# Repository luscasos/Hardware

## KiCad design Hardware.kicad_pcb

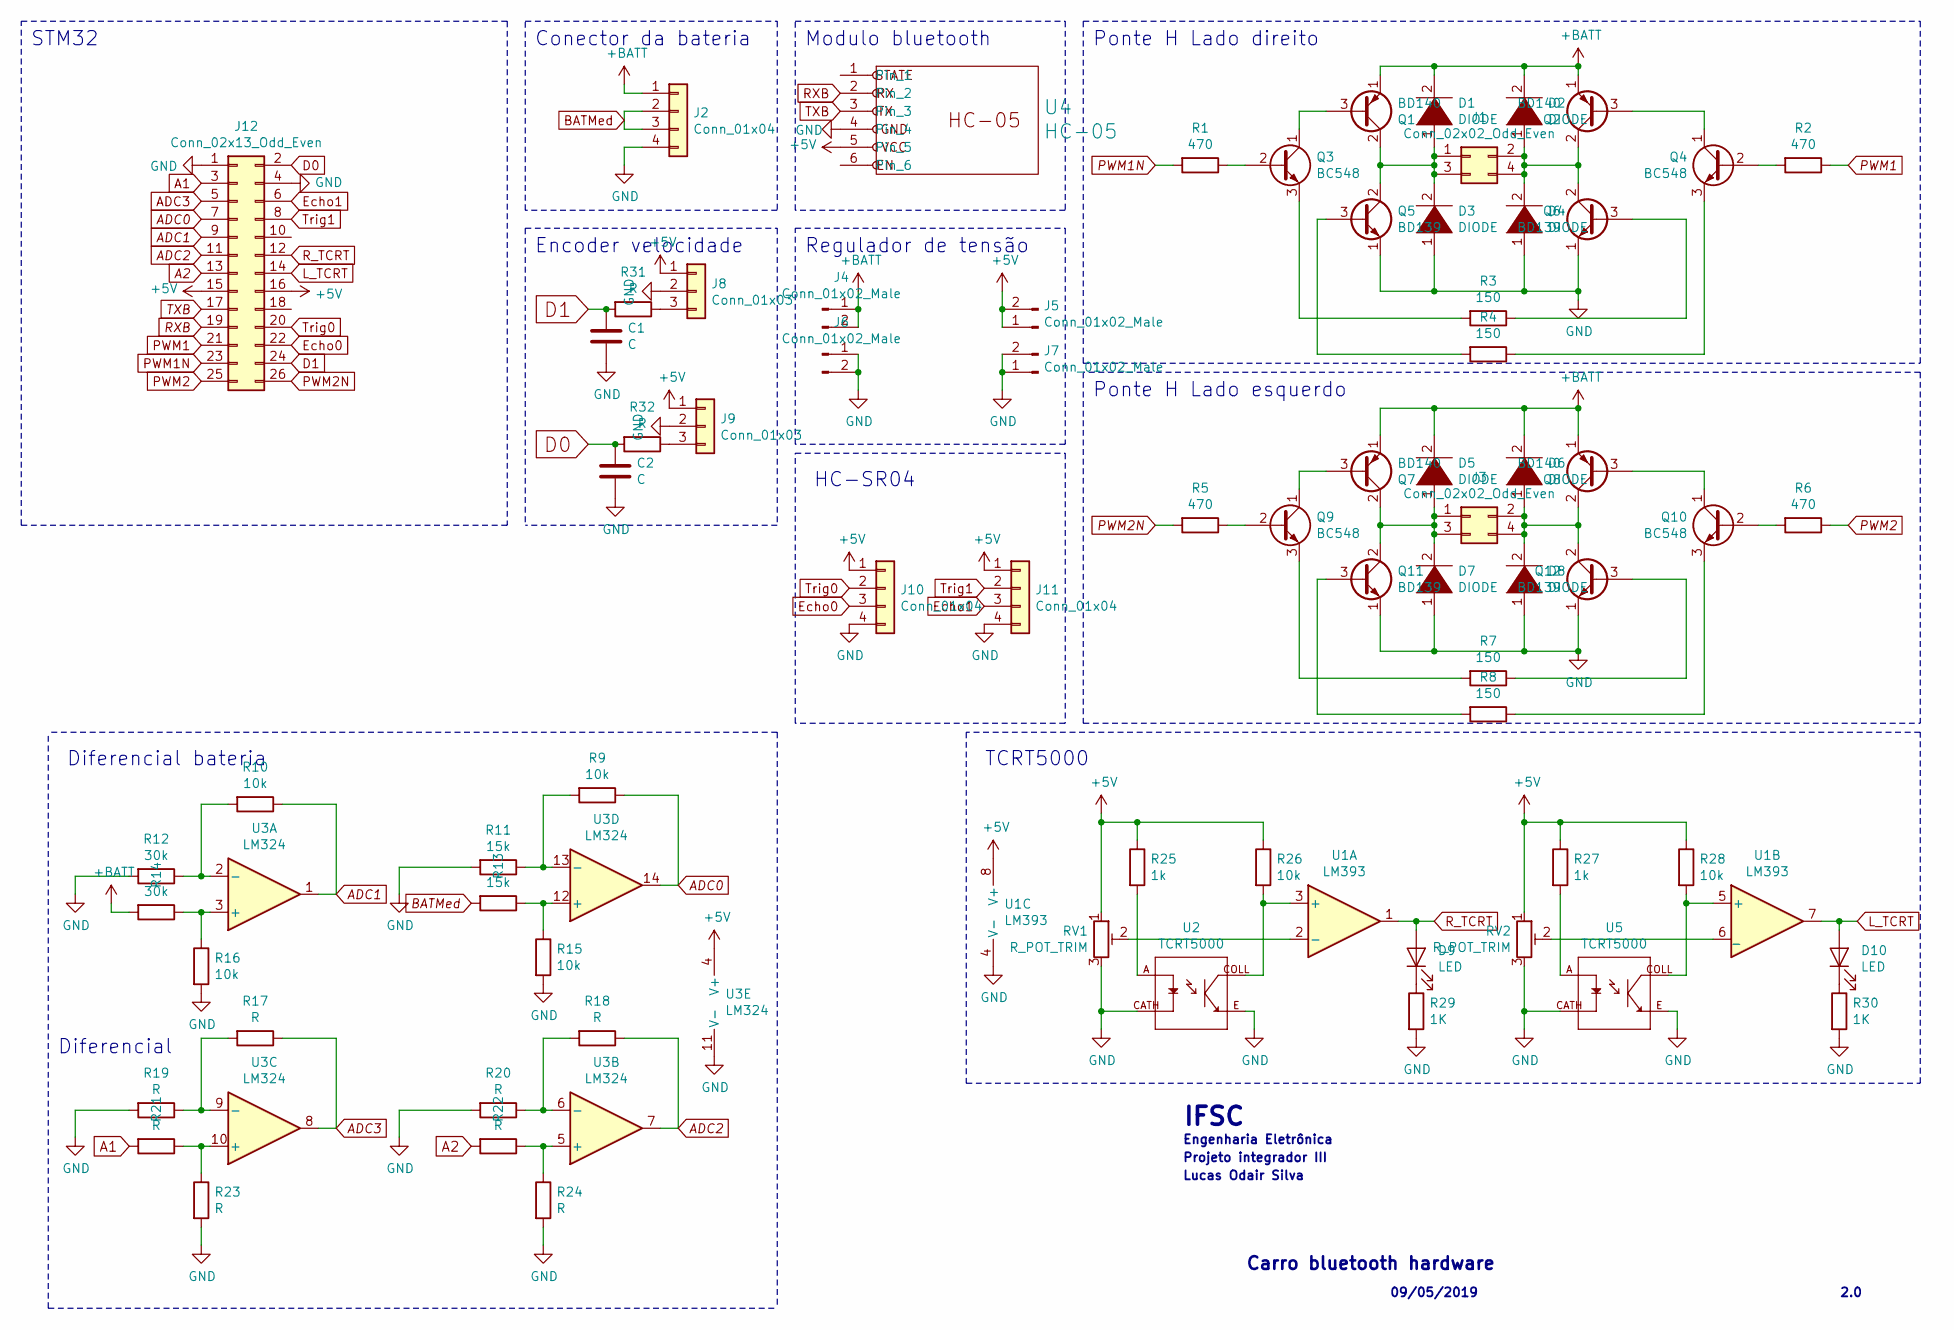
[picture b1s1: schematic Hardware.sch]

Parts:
C1, C2: C; C_0805_2012Metric_Pad1.15x1.40mm_HandSolder
D1, D2, D3, D4, D5, D6, D7, D8: DIODE; D_A-405_P2.54mm_Vertical_AnodeUp
D9, D10: LED; LED_0805_2012Metric
J1, J3: Conn_02x02_Odd_Even; PinHeader_2x02_P2.54mm_Vertical
J2, J10, J11: Conn_01x04; PinHeader_1x04_P2.54mm_Vertical
J4, J5, J6, J7: Conn_01x02_Male; PinSocket_1x02_P2.54mm_Vertical
J8, J9: Conn_01x03; PinHeader_1x03_P2.54mm_Vertical
J12: Conn_02x13_Odd_Even; PinSocket_2x13_P2.54mm_Vertical
Q1, Q2, Q7, Q8: BD140; TO-126-3_Vertical
Q3, Q4, Q9, Q10: BC548; TO-92_Inline_Wide
Q5, Q6, Q11, Q12: BD139; TO-126-3_Vertical
R1, R2, R5, R6: 470; R_0805_2012Metric
R3, R4, R7, R8: 150; R_0805_2012Metric
R9, R10, R15, R16, R26, R28: 10k; R_0805_2012Metric
R11, R13: 15k; R_0805_2012Metric
R12, R14: 30k; R_0805_2012Metric
R17, R18, R19, R20, R21, R22, R23, R24: R; R_0805_2012Metric
R25, R27: 1k; R_0805_2012Metric
R29, R30: 1K; R_0805_2012Metric
R31, R32: R; R_0805_2012Metric_Pad1.15x1.40mm_HandSolder
RV1, RV2: R_POT_TRIM; Potentiometer_Piher_PT-10-H01_Horizontal
U1: LM393
U2, U5: TCRT5000; OPTO_TCRT5000
U3: LM324; SOIC-14_3.9x8.7mm_P1.27mm
U4: HC-05; PinHeader_1x06_P2.54mm_Horizontal

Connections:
+5V: J5.1, J5.2, J8.1, J9.1, J10.1, J11.1, J12.15, J12.16, R25.1, R26.1, R27.1, R28.1, RV1.1, RV2.1, U1.8 (V+), U3.4 (V+), U4.5
+BATT: D1.2 (A), D2.2 (A), D5.2 (A), D6.2 (A), J2.1, J4.1, J4.2, Q1.1 (E), Q2.1 (E), Q7.1 (E), Q8.1 (E), R14.2
A1: J12.3, R21.2
A2: J12.13, R22.2
ADC0: J12.7, R9.1, U3.14
ADC1: J12.9, R10.1, U3.1
ADC2: J12.11, R18.1, U3.7
ADC3: J12.5, R17.1, U3.8
BATMed: J2.2, J2.3, R13.2
D0: C2.1, J12.2, R32.2
D1: C1.1, J12.24, R31.2
Echo0: J10.3, J12.22
Echo1: J11.3, J12.6
GND: C1.2, C2.2, D3.1 (K), D4.1 (K), D7.1 (K), D8.1 (K), J2.4, J6.1, J6.2, J7.1, J7.2, J8.2, J9.2, J10.4, J11.4, J12.1, J12.4, Q5.1 (E), Q6.1 (E), Q11.1 (E), Q12.1 (E), R11.2, R12.2, R15.2, R16.2, R19.2, R20.2, R23.2, R24.2, R29.2, R30.2, RV1.3, RV2.3, U1.4 (V-), U2.CATH, U2.E, U3.11 (V-), U4.4, U5.CATH, U5.E
L_TCRT: D10.2 (A), J12.14, U1.7
unnamed: D1.1 (K), D3.2 (A), J1.1, J1.3, Q1.2 (C), Q5.2 (C)
unnamed: D2.1 (K), D4.2 (A), J1.2, J1.4, Q2.2 (C), Q6.2 (C)
unnamed: D5.1 (K), D7.2 (A), J3.1, J3.3, Q7.2 (C), Q11.2 (C)
unnamed: D6.1 (K), D8.2 (A), J3.2, J3.4, Q8.2 (C), Q12.2 (C)
unnamed: D9.1 (K), R29.1
unnamed: D10.1 (K), R30.1
unnamed: J8.3, R31.1
unnamed: J9.3, R32.1
unnamed: Q1.3 (B), Q3.1 (C)
unnamed: Q2.3 (B), Q4.1 (C)
unnamed: Q3.2 (B), R1.1
unnamed: Q3.3 (E), R3.2
unnamed: Q4.2 (B), R2.2
unnamed: Q4.3 (E), R4.1
unnamed: Q5.3 (B), R4.2
unnamed: Q6.3 (B), R3.1
unnamed: Q7.3 (B), Q9.1 (C)
unnamed: Q9.2 (B), R5.1
unnamed: Q9.3 (E), R7.2
unnamed: Q8.3 (B), Q10.1 (C)
unnamed: Q10.2 (B), R6.2
unnamed: Q10.3 (E), R8.1
unnamed: Q11.3 (B), R8.2
unnamed: Q12.3 (B), R7.1
unnamed: R10.2, R12.1, U3.2 (-)
unnamed: R9.2, R11.1, U3.13 (-)
unnamed: R13.1, R15.1, U3.12 (+)
unnamed: R14.1, R16.1, U3.3 (+)
unnamed: R17.2, R19.1, U3.9 (-)
unnamed: R18.2, R20.1, U3.6 (-)
unnamed: R21.1, R23.1, U3.10 (+)
unnamed: R22.1, R24.1, U3.5 (+)
unnamed: R25.2, U2.A
unnamed: R26.2, U1.3 (+), U2.COLL
unnamed: R27.2, U5.A
unnamed: R28.2, U1.5 (+), U5.COLL
unnamed: RV1.2, U1.2 (-)
unnamed: RV2.2, U1.6 (_)
PWM1: J12.21, R2.1
PWM1N: J12.23, R1.2
PWM2: J12.25, R6.1
PWM2N: J12.26, R5.2
RXB: J12.19, U4.2
R_TCRT: D9.2 (A), J12.12, U1.1
TXB: J12.17, U4.3
Trig0: J10.2, J12.20
Trig1: J11.2, J12.8

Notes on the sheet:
Carro bluetooth hardware
09/05/2019
2.0
IFSC
Projeto integrador III
Lucas Odair Silva
Engenharia Eletrônica
Ponte H Lado direito
Ponte H Lado esquerdo
Diferencial bateria
Modulo bluetooth
Conector da bateria
Regulador de tensão
STM32
Encoder velocidade
Diferencial
HC-SR04
TCRT5000

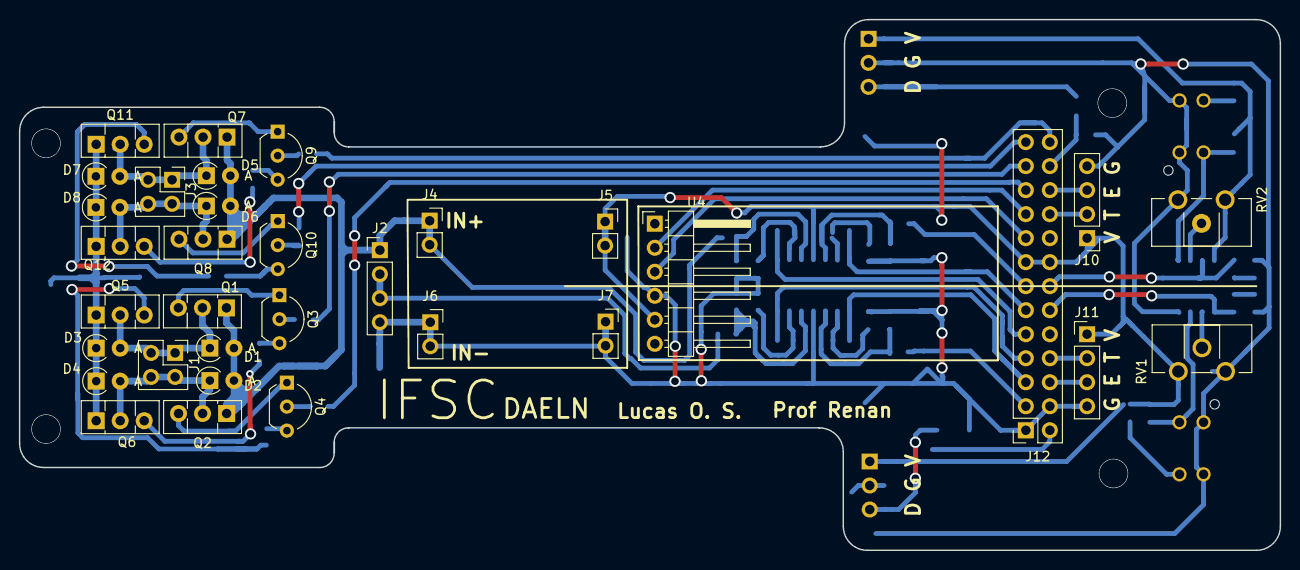
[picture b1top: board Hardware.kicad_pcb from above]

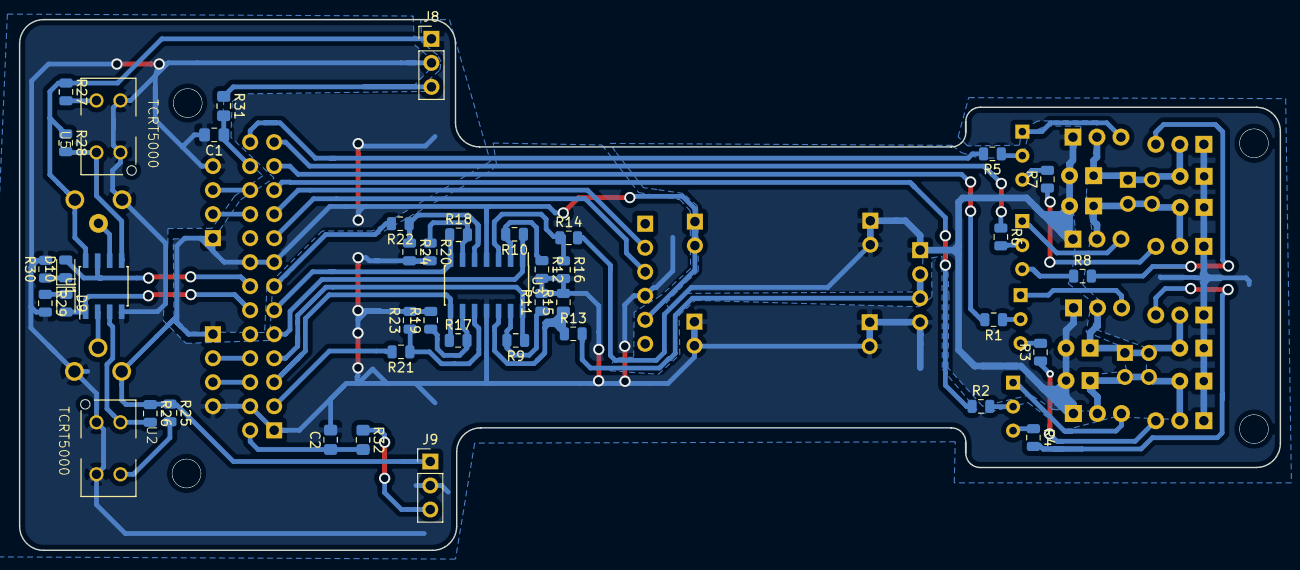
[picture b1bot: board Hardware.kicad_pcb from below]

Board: 2 copper layers, 133.3 x 56.1 mm, 75 parts (42 on the bottom side), 62 nets.
